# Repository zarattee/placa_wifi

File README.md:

# placa_wifi
 placa con un d1 mini y 8 relay

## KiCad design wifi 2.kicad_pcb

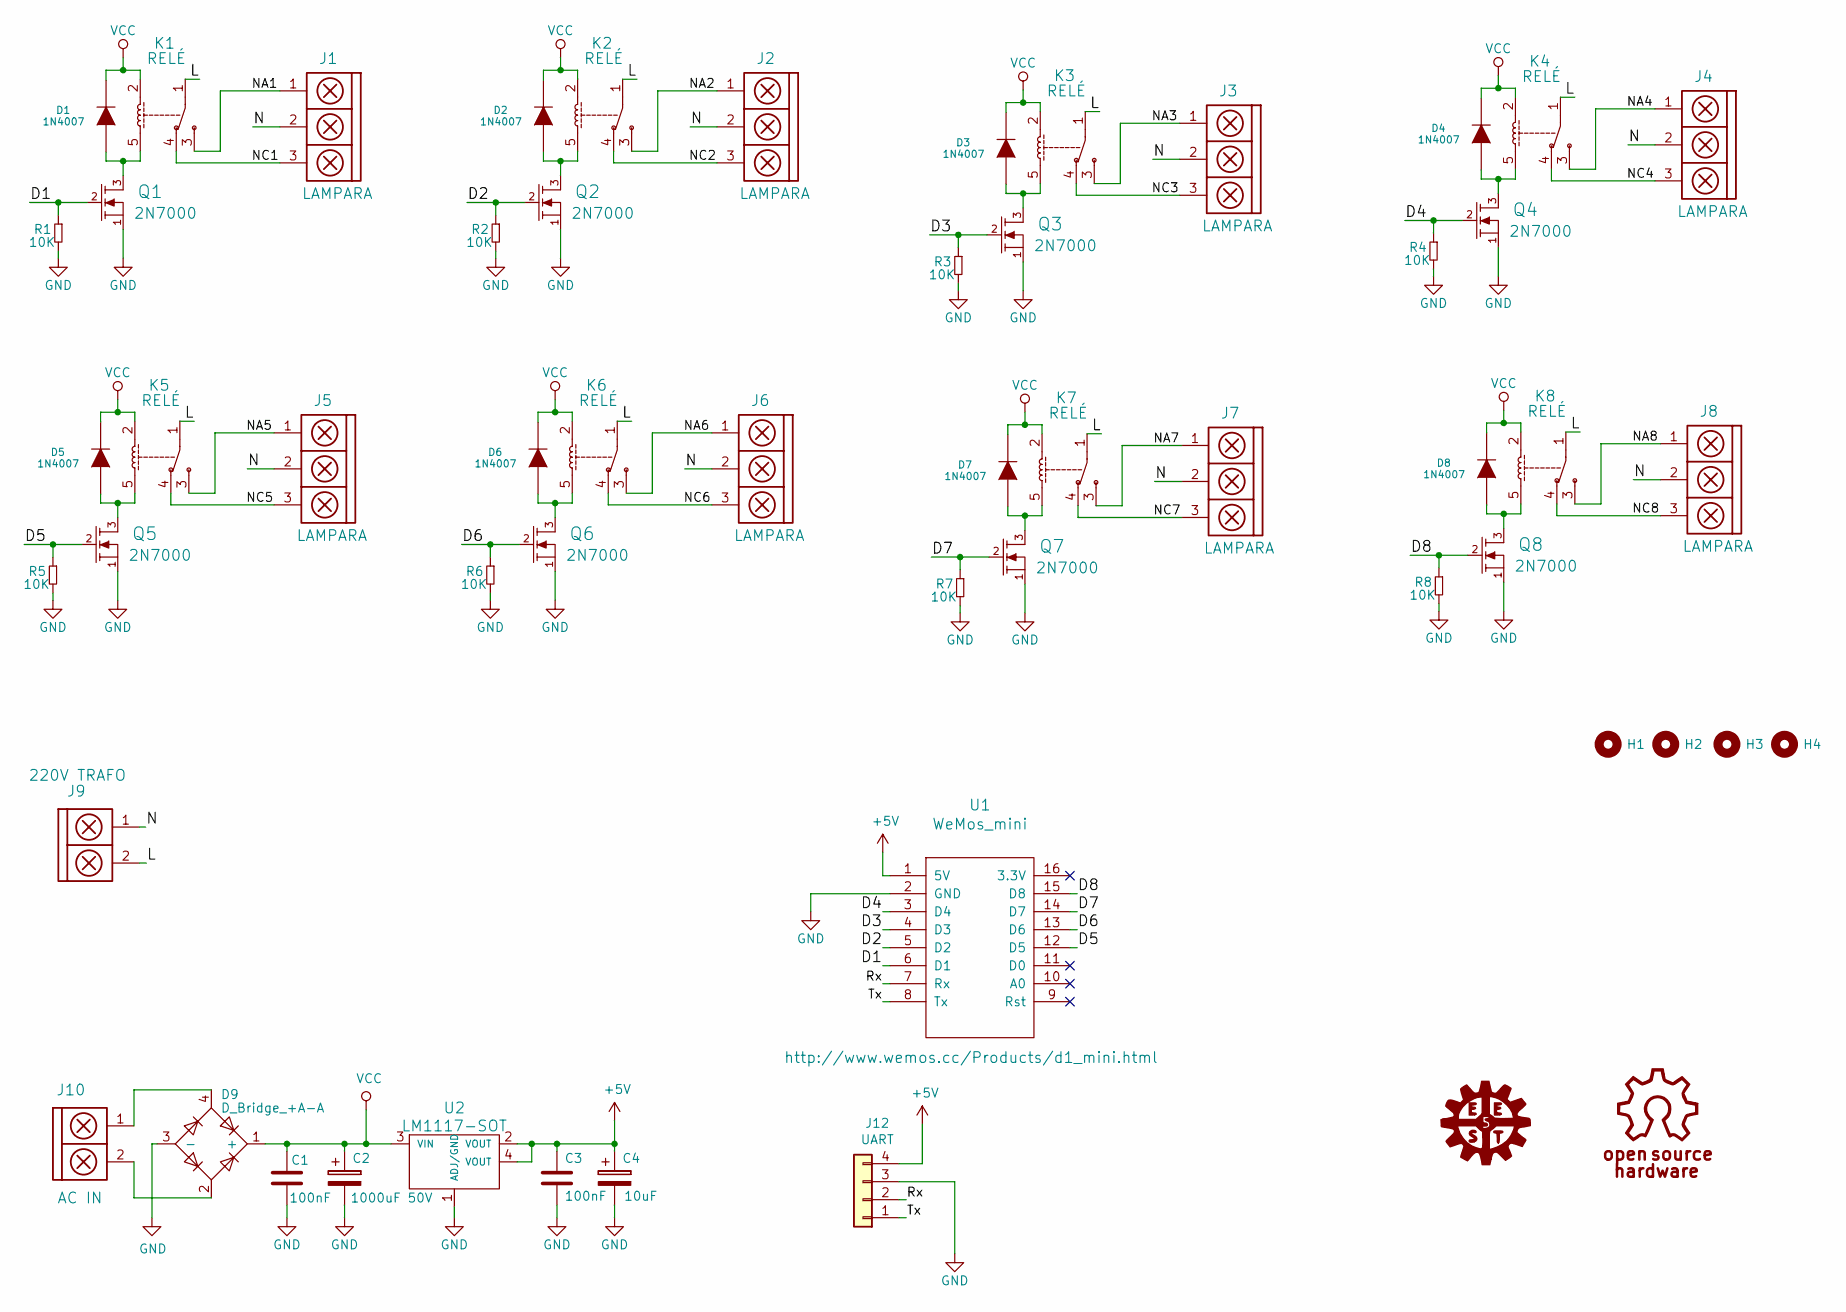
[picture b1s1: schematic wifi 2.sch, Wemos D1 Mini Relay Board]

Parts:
C1, C3: 100nF; C_1206
C2: 1000uF 50V; CAP_ELEC_8x11.5mm
C4: 10uF; CAP_ELEC_5x11mm
D1, D2, D3, D4, D5, D6, D7, D8: 1N4007; sod123
D9: D_Bridge_+A-A; Diode_Bridge_Round_D8.9mm
H1, H2, H3, H4: Mounting_Hole; Separador_M3_5mm
J1, J2, J3, J4, J5, J6, J7, J8: LAMPARA; BORNERA3_AZUL
J9: 220V TRAFO; BORNERA2_AZUL
J10: AC IN; BORNERA2_AZUL
J12: UART; pin_strip_4
K1, K2, K3, K4, K5, K6, K7, K8: RELÉ; Relay_C
Q1, Q2, Q3, Q4, Q5, Q6, Q7, Q8: 2N7000; SOT23
R1, R2, R3, R4, R5, R6, R7, R8: 10K; R_1206
U1: WeMos_mini; Wemos_D1_Mini_Board
U2: LM1117-SOT; SOT223

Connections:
+5V: C3.1, C4.1, J12.4, U1.1 (5V), U2.2 (VOUT), U2.4 (VOUT); also elsewhere on the board
/D1: Q1.2 (G), R1.1, U1.6 (D1)
/D2: Q2.2 (G), R2.1, U1.5 (D2)
/D3: Q3.2 (G), R3.1, U1.4 (D3)
/D4: Q4.2 (G), R4.1, U1.3 (D4)
/D5: Q5.2 (G), R5.1, U1.12 (D5)
/D6: Q6.2 (G), R6.1, U1.13 (D6)
/D7: Q7.2 (G), R7.1, U1.14 (D7)
/D8: Q8.2 (G), R8.1, U1.15 (D8)
/L: J9.2, K1.1, K2.1, K3.1, K4.1, K5.1, K6.1, K7.1, K8.1
/N: J1.2, J2.2, J3.2, J4.2, J5.2, J6.2, J7.2, J8.2, J9.1; also elsewhere on the board
/NA1: J1.1, K1.3
/NA2: J2.1, K2.3
/NA3: J3.1, K3.3; also elsewhere on the board
/NA4: J4.1, K4.3
/NA5: J5.1, K5.3
/NA6: J6.1, K6.3
/NA7: J7.1, K7.3
/NA8: J8.1, K8.3
/NC1: J1.3, K1.4
/NC2: J2.3, K2.4
/NC3: J3.3, K3.4; also elsewhere on the board
/NC4: J4.3, K4.4
/NC5: J5.3, K5.4
/NC6: J6.3, K6.4
/NC7: J7.3, K7.4
/NC8: J8.3, K8.4
/Rx: J12.2, U1.7 (Rx); also elsewhere on the board
/Tx: J12.1, U1.8 (Tx); also elsewhere on the board
GND: C1.2, C2.2, C3.2, C4.2, D9.3 (-), J12.3, Q1.1 (S), Q2.1 (S), Q3.1 (S), Q4.1 (S), Q5.1 (S), Q6.1 (S), Q7.1 (S), Q8.1 (S), R1.2, R2.2, R3.2, R4.2, R5.2, R6.2, R7.2, R8.2, U1.2 (GND), U2.1 (ADJ/GND); also elsewhere on the board
unnamed: D1.1 (A), K1.5, Q1.3 (D)
unnamed: D2.1 (A), K2.5, Q2.3 (D)
unnamed: D3.1 (A), K3.5, Q3.3 (D)
unnamed: D4.1 (A), K4.5, Q4.3 (D)
unnamed: D5.1 (A), K5.5, Q5.3 (D)
unnamed: D6.1 (A), K6.5, Q6.3 (D)
unnamed: D7.1 (A), K7.5, Q7.3 (D)
unnamed: D8.1 (A), K8.5, Q8.3 (D)
unnamed: D9.2, J10.2
unnamed: D9.4, J10.1
VCC: C1.1, C2.1, D1.2 (K), D2.2 (K), D3.2 (K), D4.2 (K), D5.2 (K), D6.2 (K), D7.2 (K), D8.2 (K), D9.1 (+), K1.2, K2.2, K3.2, K4.2, K5.2, K6.2, K7.2, K8.2, U2.3 (VIN)

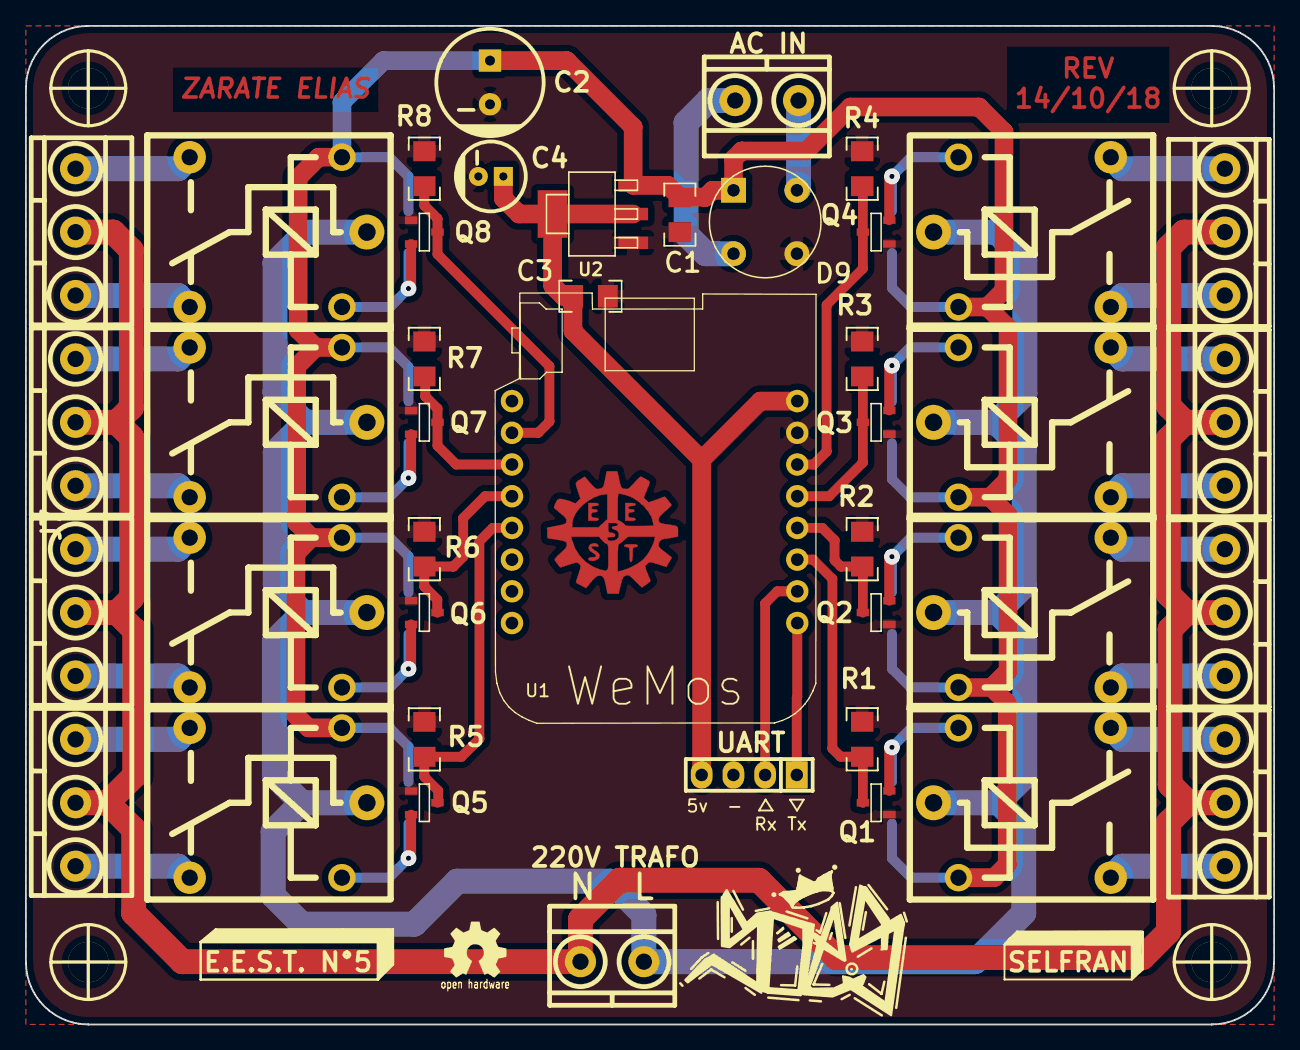
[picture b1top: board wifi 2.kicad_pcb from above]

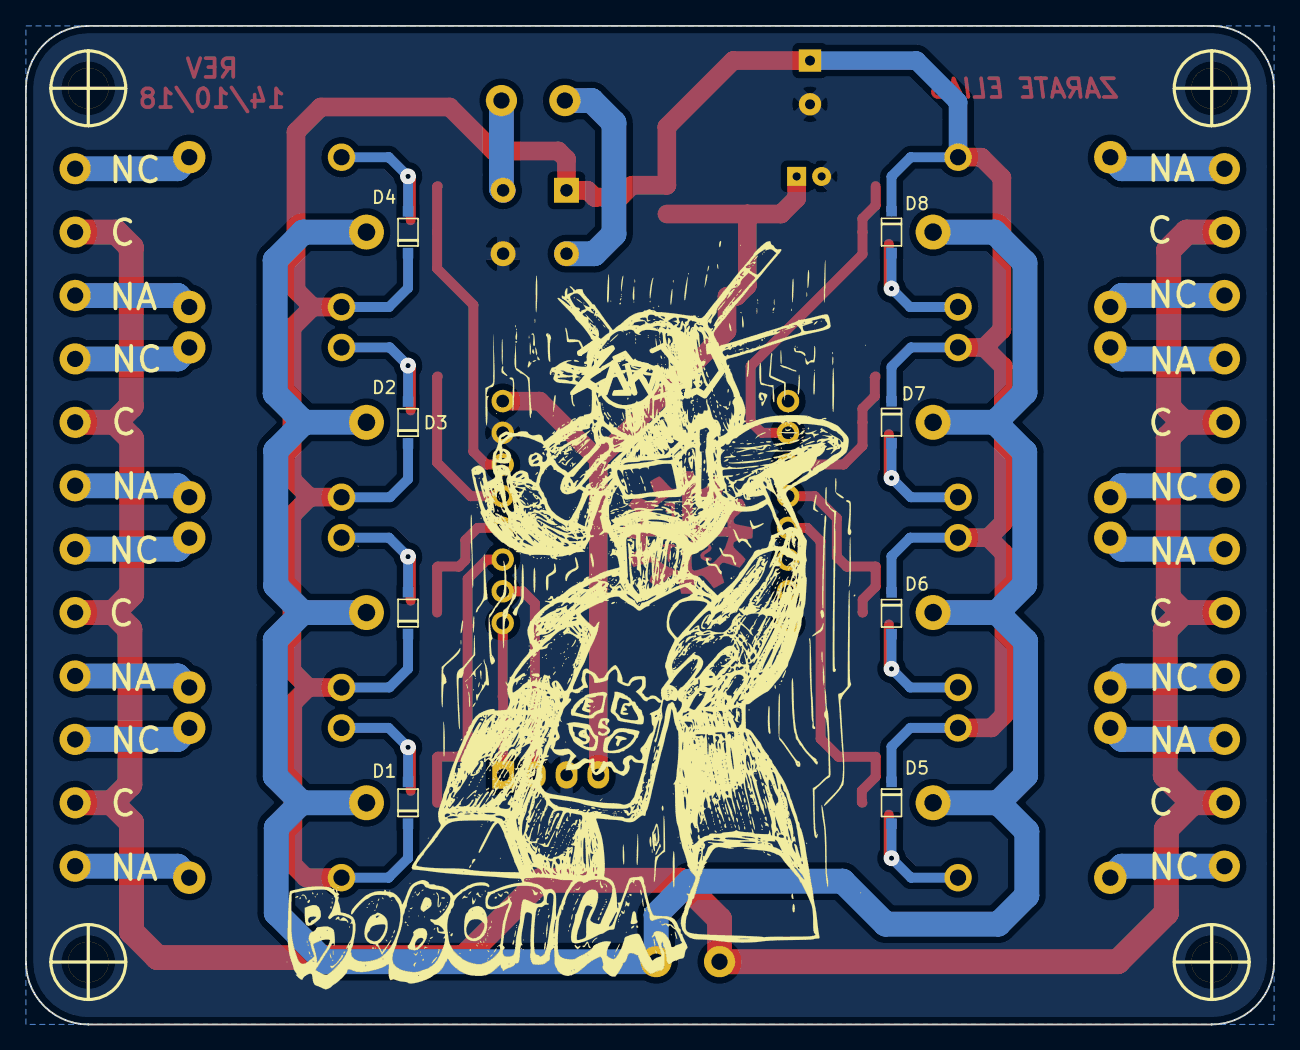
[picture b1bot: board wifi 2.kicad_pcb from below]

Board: 2 copper layers, 100.0 x 80.0 mm, 54 parts (8 on the bottom side), 41 nets.

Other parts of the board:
UART: UART; pin_strip_4
eJ3: LAMPARA; BORNERA3_AZUL

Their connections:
+5V: UART.4; also elsewhere on the board
/N: eJ3.2; also elsewhere on the board
/NA3: eJ3.1; also elsewhere on the board
/NC3: eJ3.3; also elsewhere on the board
/Rx: UART.2; also elsewhere on the board
/Tx: UART.1; also elsewhere on the board
GND: UART.3; also elsewhere on the board

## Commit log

2020-11-02 placa con wifi para controlar 8 relays
    placa con conectividad wifi:
    cuenta con 8 reles
    uart
2020-11-04 Cambios estructura de archivos
    Reorganización de carpetas del proyecto:
    +gerber
    +bom
    +img
    Eliminé archivos en conflicto heredados de dropbox y cambié el nombre del SCH en formato PDF.
2021-01-14 Vista 3D
    Agrego archivo de la vista 3D
